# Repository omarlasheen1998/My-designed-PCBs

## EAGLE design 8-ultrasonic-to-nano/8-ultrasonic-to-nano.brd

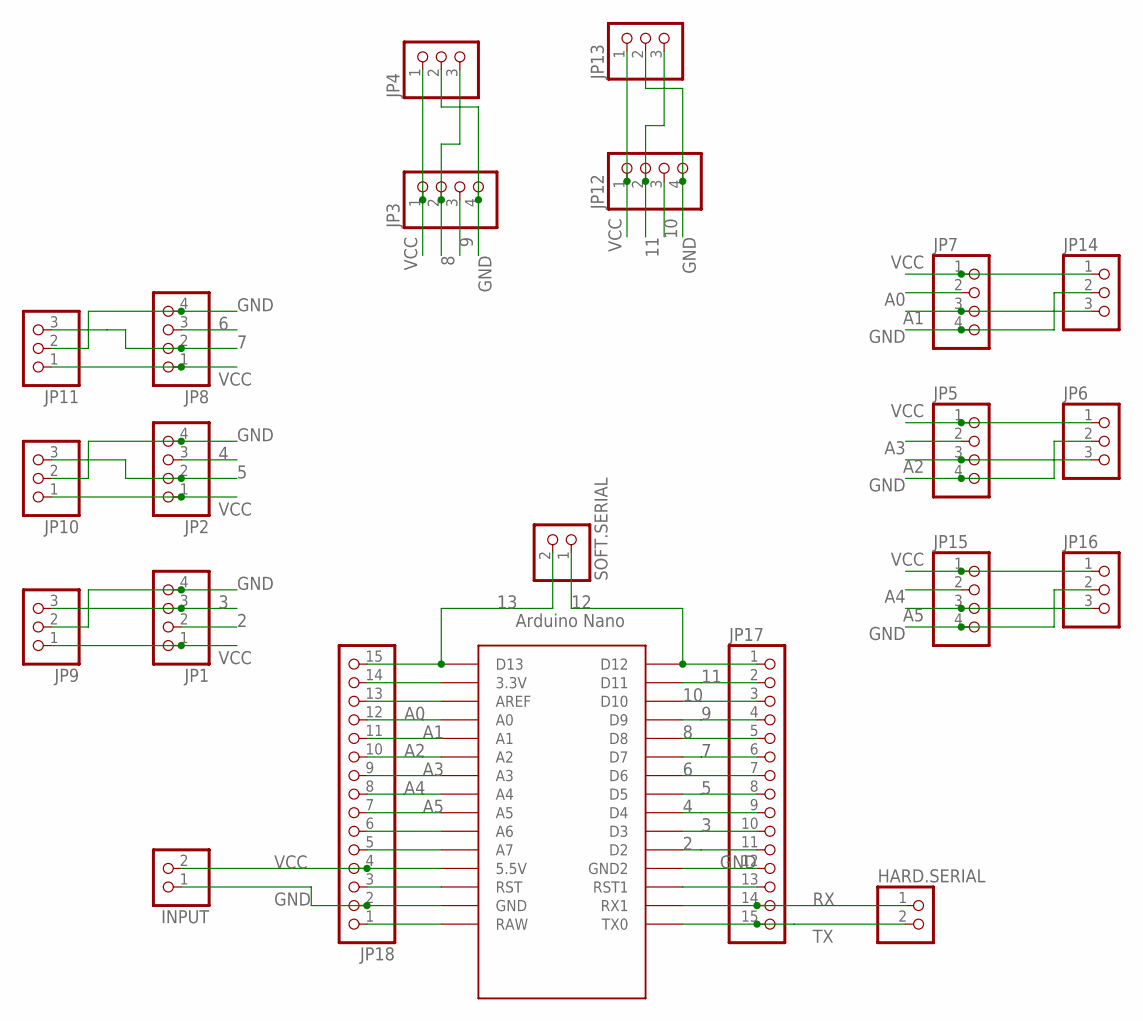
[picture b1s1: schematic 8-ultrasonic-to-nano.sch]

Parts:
HARD.SERIAL: PINHD-2_DATA; 1X02_DATA
INPUT: PINHD-2_DATA; 1X02_DATA
JP1, JP2, JP3, JP5, JP7, JP8, JP12, JP15: PINHD-4_DATA; 1X04_DATA
JP4, JP6, JP9, JP10, JP11, JP13, JP14, JP16: PINHD-3_DATA; 1X03_DATA
JP17, JP18: PINHD-1X15; 1X15
SOFT.SERIAL: PINHD-2_DATA; 1X02_DATA
U$1: ARDUINO_NANO; NANO

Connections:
2: JP1.2, JP17.11, U$1.D2
3: JP1.3, JP9.3, JP17.10, U$1.D3
4: JP2.3, JP17.9, U$1.D4
5: JP2.2, JP10.3, JP17.8, U$1.D5
6: JP8.3, JP17.7, U$1.D6
7: JP8.2, JP11.3, JP17.6, U$1.D7
8: JP3.2, JP4.3, JP17.5, U$1.D8
9: JP3.3, JP17.4, U$1.D9
10: JP12.3, JP17.3, U$1.D10
11: JP12.2, JP13.3, JP17.2, U$1.D11
12: JP17.1, SOFT.SERIAL.1, U$1.D12
13: JP18.15, SOFT.SERIAL.2, U$1.D13
A0: JP7.2, JP18.12, U$1.A0
A1: JP7.3, JP14.3, JP18.11, U$1.A1
A2: JP5.3, JP6.3, JP18.10, U$1.A2
A3: JP5.2, JP18.9, U$1.A3
A4: JP15.2, JP18.8, U$1.A4
A5: JP15.3, JP16.3, JP18.7, U$1.A5
GND: INPUT.1, JP1.4, JP2.4, JP3.4, JP4.2, JP5.4, JP6.2, JP7.4, JP8.4, JP9.2, JP10.2, JP11.2, JP12.4, JP13.2, JP14.2, JP15.4, JP16.2, JP17.12, JP18.2, U$1.GND, U$1.GND1 (GND2)
unnamed: JP17.13, U$1.RST1
unnamed: JP18.14, U$1.3.3V
unnamed: JP18.13, U$1.AREF
unnamed: JP18.6, U$1.A6
unnamed: JP18.5, U$1.A7
unnamed: JP18.3, U$1.RST
unnamed: JP18.1, U$1.RAW
RX: HARD.SERIAL.1, JP17.14, U$1.RX1
TX: HARD.SERIAL.2, JP17.15, U$1.TX0
VCC: INPUT.2, JP1.1, JP2.1, JP3.1, JP4.1, JP5.1, JP6.1, JP7.1, JP8.1, JP9.1, JP10.1, JP11.1, JP12.1, JP13.1, JP14.1, JP15.1, JP16.1, JP18.4, U$1.5V (5.5V)

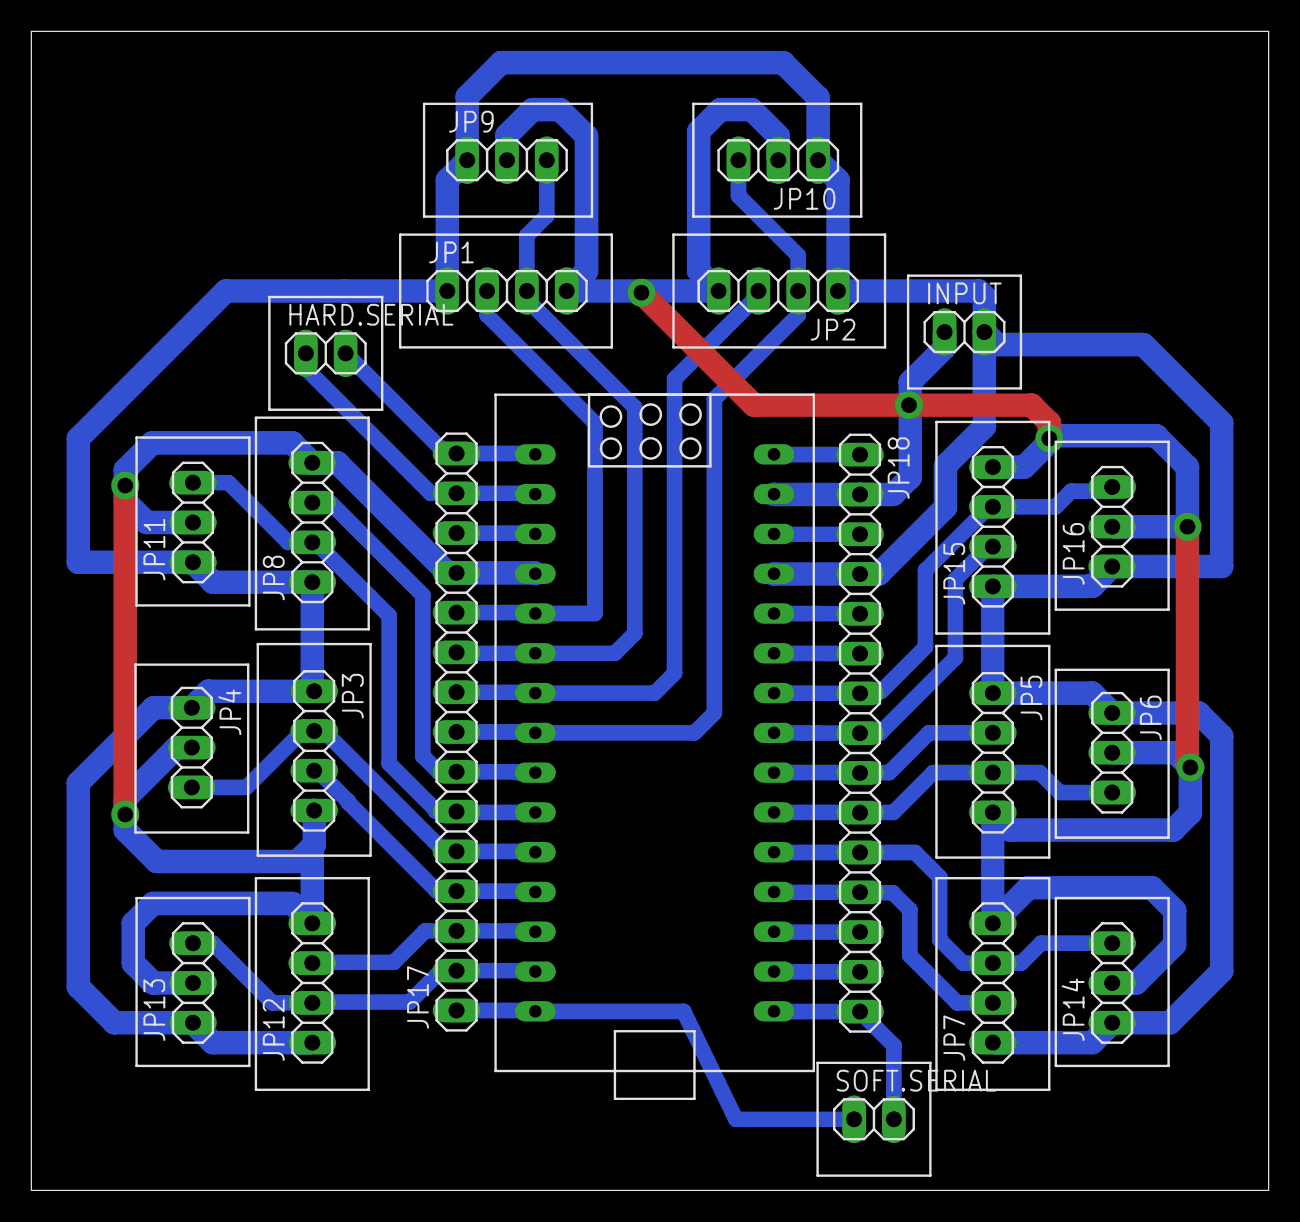
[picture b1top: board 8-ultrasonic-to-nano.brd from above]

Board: 2 copper layers, 79.0 x 74.0 mm, 22 parts (0 on the bottom side), 29 nets.

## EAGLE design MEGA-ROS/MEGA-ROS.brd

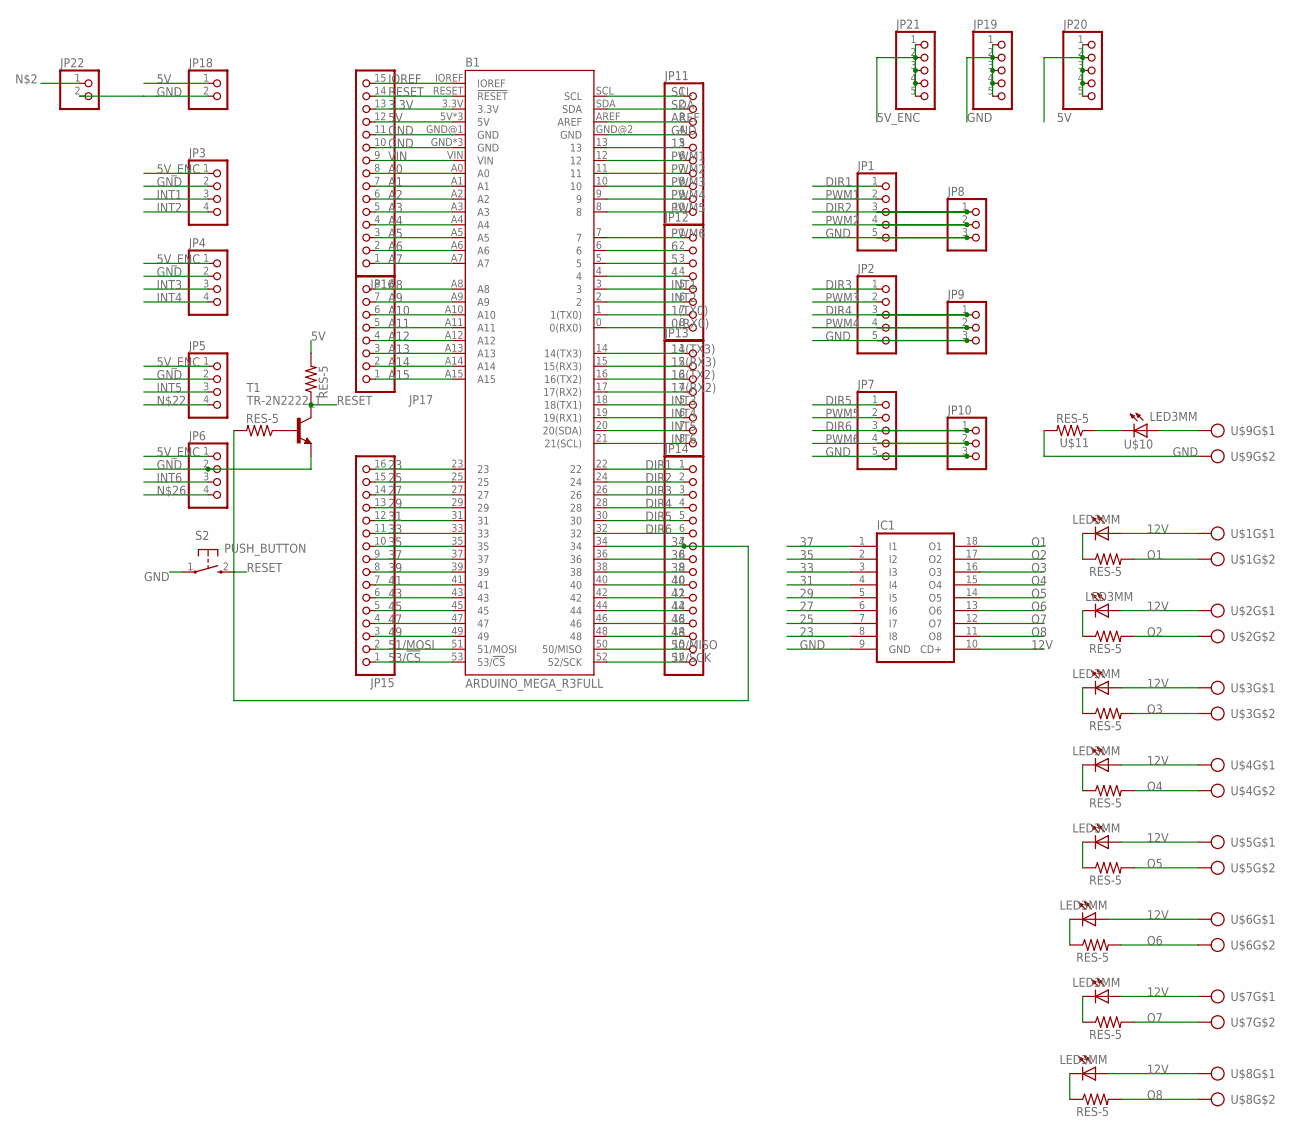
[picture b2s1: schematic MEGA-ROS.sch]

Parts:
B1: ARDUINO_MEGA_R3FULL; ARDUINO_MEGA_NO_SILK
IC1: ULN2803A; DIL18
JP1, JP2, JP7: PINHD-5_DATA; 1X05_DATA
JP3, JP4, JP5, JP6: PINHD-4_DATA; 1X04_DATA
JP8, JP9, JP10: PINHD-3_DATA; 1X03_DATA
JP11: PINHD-1X10; 1X10
JP12, JP13, JP17: PINHD-1X8; 1X08
JP14, JP15: PINHD-1X16; 1X16
JP16: PINHD-1X15; 1X15
JP18, JP22: PINHD-2_DATA; 1X02_DATA
JP19, JP20, JP21: PINHD-1X5; 1X05
S2: PUSH_BUTTON; B3F-10XX
T1: TR-2N2222_1; TO92-EBC
U$1, U$2, U$3, U$4, U$5, U$6, U$7, U$8, U$9: CON_PTR_2; AK300/2
U$10, U$12, U$14, U$16, U$18, U$20, U$22, U$24, U$26: LED3MM
U$11, U$13, U$15, U$17, U$19, U$21, U$23, U$25, U$27, U$28, U$29: RES-5; 0204/5

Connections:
0(RX0): B1.0 (0(RX0)), JP12.8
1(TX0): B1.1 (1(TX0)), JP12.7
3.3V: B1.3.3V, JP16.13
4: B1.4, JP12.4
5: B1.5, JP12.3
5V: B1.5V, B1.5V@1 (5V), B1.5V@2 (5V), JP16.12, JP18.1, JP20.1, JP20.2, JP20.3, JP20.4, JP20.5, U$28.2
5V_ENC: JP3.1, JP4.1, JP5.1, JP6.1, JP21.1, JP21.2, JP21.3, JP21.4, JP21.5
6: B1.6, JP12.2
12V: IC1.10 (CD+), U$1.1, U$2.1, U$3.1, U$4.1, U$5.1, U$6.1, U$7.1, U$8.1, U$12.A, U$14.A, U$16.A, U$18.A, U$20.A, U$22.A, U$24.A, U$26.A
13: B1.13, JP11.5
14(TX3): B1.14 (14(TX3)), JP13.1
15(RX3): B1.15 (15(RX3)), JP13.2
16(TX2): B1.16 (16(TX2)), JP13.3
17(RX2): B1.17 (17(RX2)), JP13.4
23: B1.23, IC1.8 (I8), JP15.16
25: B1.25, IC1.7 (I7), JP15.15
27: B1.27, IC1.6 (I6), JP15.14
29: B1.29, IC1.5 (I5), JP15.13
31: B1.31, IC1.4 (I4), JP15.12
33: B1.33, IC1.3 (I3), JP15.11
34: B1.34, JP14.7, U$29.2
35: B1.35, IC1.2 (I2), JP15.10
36: B1.36, JP14.8
37: B1.37, IC1.1 (I1), JP15.9
38: B1.38, JP14.9
39: B1.39, JP15.8
40: B1.40, JP14.10
41: B1.41, JP15.7
42: B1.42, JP14.11
43: B1.43, JP15.6
44: B1.44, JP14.12
45: B1.45, JP15.5
46: B1.46, JP14.13
47: B1.47, JP15.4
48: B1.48, JP14.14
49: B1.49, JP15.3
50/MISO: B1.50 (50/MISO), JP14.15
51/MOSI: B1.51 (51/MOSI), JP15.2
52/SCK: B1.52 (52/SCK), JP14.16
53/!CS: B1.53 (53/!CS), JP15.1
A0: B1.A0, JP16.8
A1: B1.A1, JP16.7
A2: B1.A2, JP16.6
A3: B1.A3, JP16.5
A4: B1.A4, JP16.4
A5: B1.A5, JP16.3
A6: B1.A6, JP16.2
A7: B1.A7, JP16.1
A8: B1.A8, JP17.8
A9: B1.A9, JP17.7
A10: B1.A10, JP17.6
A11: B1.A11, JP17.5
A12: B1.A12, JP17.4
A13: B1.A13, JP17.3
A14: B1.A14, JP17.2
A15: B1.A15, JP17.1
AREF: B1.AREF, JP11.3
DIR1: B1.22, JP1.1, JP14.1
DIR2: B1.24, JP1.3, JP8.1, JP14.2
DIR3: B1.26, JP2.1, JP14.3
DIR4: B1.28, JP2.3, JP9.1, JP14.4
DIR5: B1.30, JP7.1, JP14.5
DIR6: B1.32, JP7.3, JP10.1, JP14.6
GND: B1.GND, B1.GND@1 (GND), B1.GND@2 (GND), B1.GND@3 (GND), B1.GND@4 (GND), IC1.9 (GND), JP1.5, JP2.5, JP3.2, JP4.2, JP5.2, JP6.2, JP7.5, JP8.3, JP9.3, JP10.3, JP11.4, JP16.10, JP16.11, JP18.2, JP19.1, JP19.2, JP19.3, JP19.4, JP19.5, JP22.2, S2.1, T1.E, U$9.2, U$11.2
INT1: B1.3, JP3.3, JP12.5
INT2: B1.2, JP3.4, JP12.6
INT3: B1.18 (18(TX1)), JP4.3, JP13.5
INT4: B1.19 (19(RX1)), JP4.4, JP13.6
INT5: B1.20 (20(SDA)), JP5.3, JP13.7
INT6: B1.21 (21(SCL)), JP6.3, JP13.8
IOREF: B1.IOREF, JP16.15
unnamed: U$10.K (C), U$11.1
unnamed: U$12.K (C), U$13.1
unnamed: U$14.K (C), U$15.1
unnamed: U$16.K (C), U$17.1
unnamed: U$18.K (C), U$19.1
unnamed: U$20.K (C), U$21.1
unnamed: U$22.K (C), U$23.1
unnamed: U$24.K (C), U$25.1
unnamed: U$26.K (C), U$27.1
unnamed: U$9.1, U$10.A
unnamed: T1.B, U$29.1
O1: IC1.18 (O1), U$1.2, U$13.2
O2: IC1.17 (O2), U$2.2, U$15.2
O3: IC1.16 (O3), U$3.2, U$17.2
O4: IC1.15 (O4), U$4.2, U$19.2
O5: IC1.14 (O5), U$5.2, U$21.2
O6: IC1.13 (O6), U$6.2, U$23.2
O7: IC1.12 (O7), U$7.2, U$25.2
O8: IC1.11 (O8), U$8.2, U$27.2
PWM1: B1.12, JP1.2, JP11.6
PWM2: B1.11, JP1.4, JP8.2, JP11.7
PWM3: B1.10, JP2.2, JP11.8
PWM4: B1.9, JP2.4, JP9.2, JP11.9
PWM5: B1.8, JP7.2, JP11.10
PWM6: B1.7, JP7.4, JP10.2, JP12.1
RESET: B1.RESET (!RESET), JP16.14, S2.2 (S), T1.C, U$28.1
SCL: B1.SCL, JP11.1
SDA: B1.SDA, JP11.2
VIN: B1.VIN, JP16.9

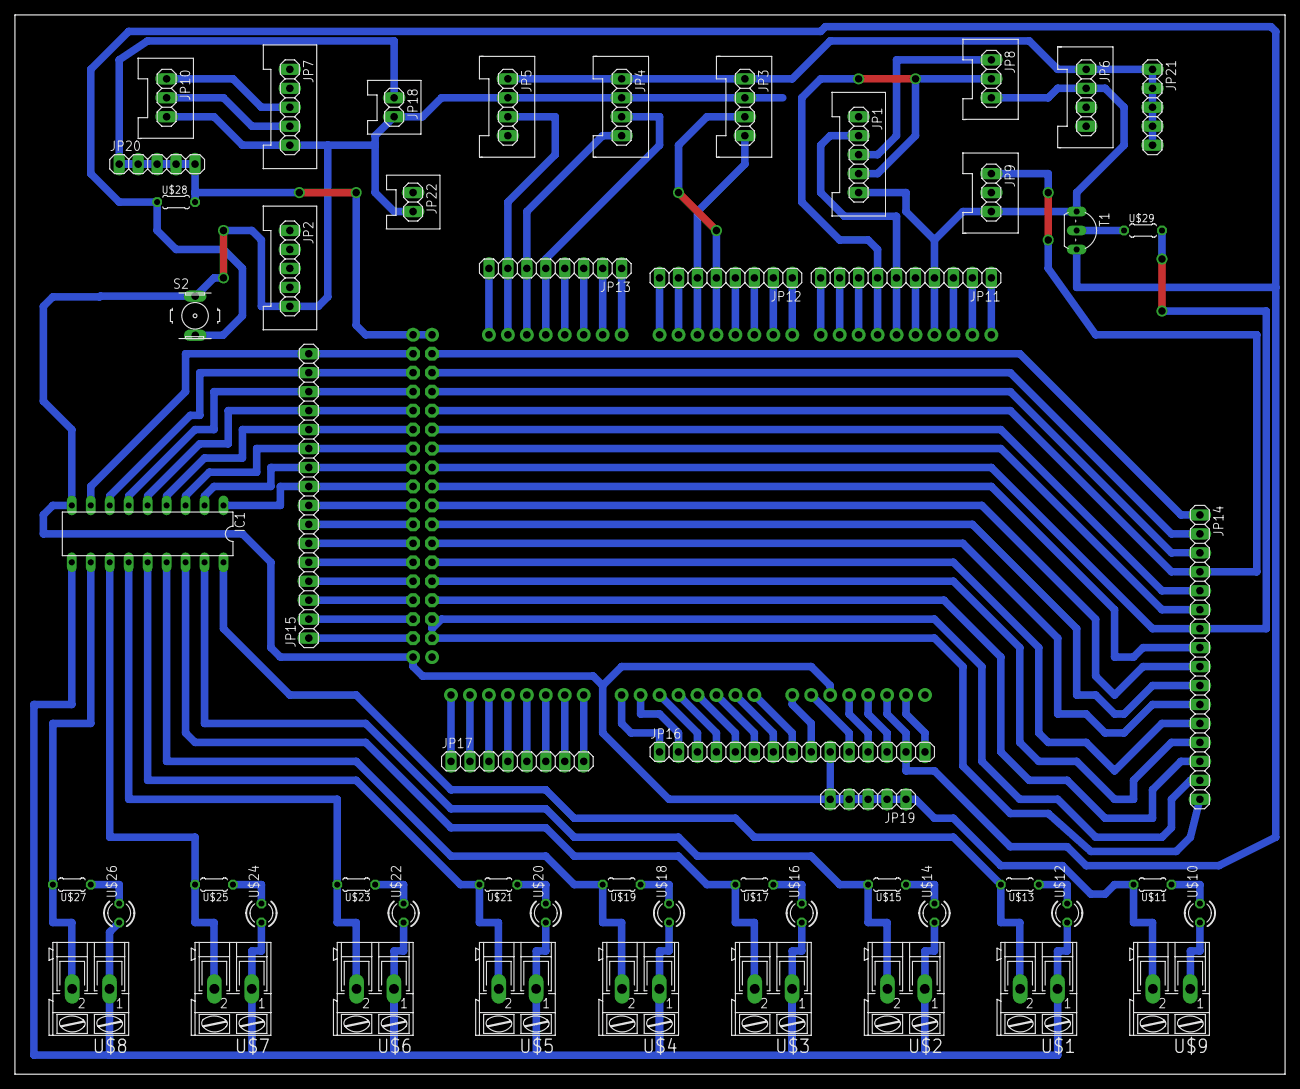
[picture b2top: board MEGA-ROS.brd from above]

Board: 2 copper layers, 170.2 x 141.9 mm, 55 parts (1 on the bottom side), 100 nets.

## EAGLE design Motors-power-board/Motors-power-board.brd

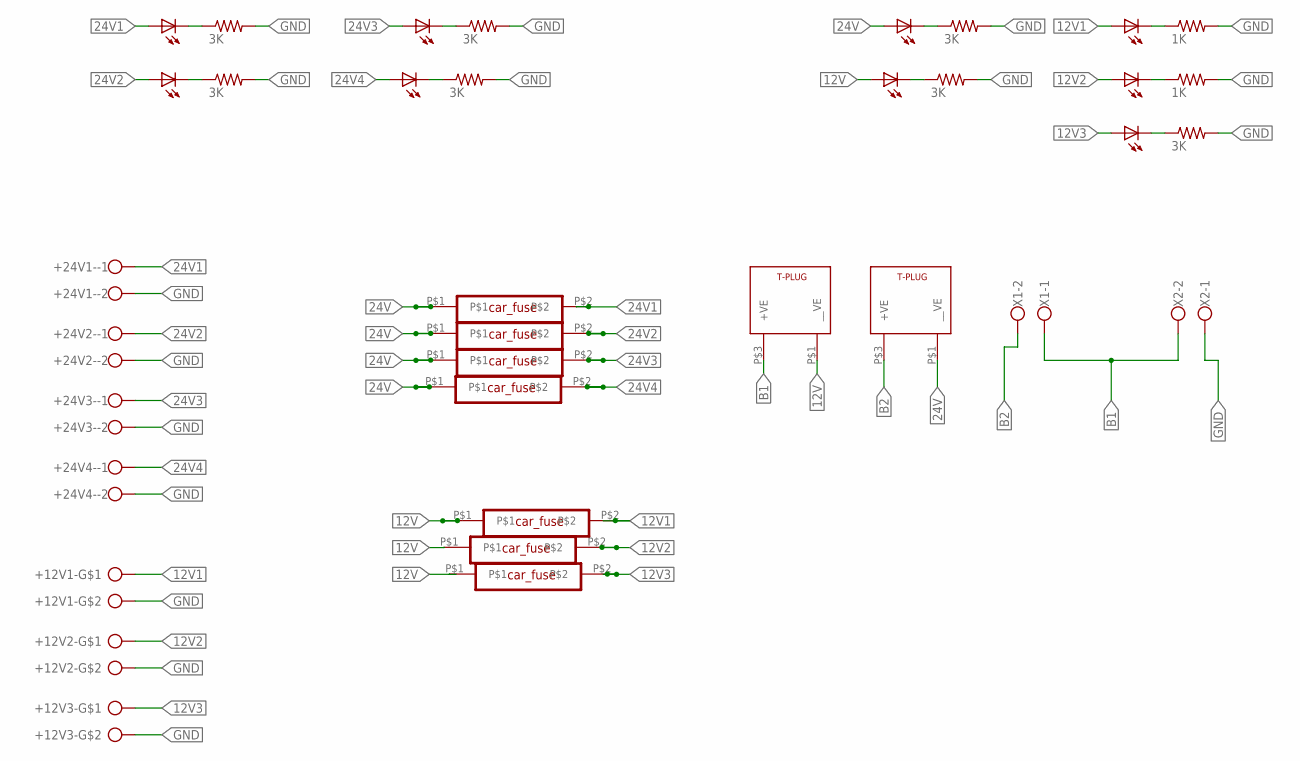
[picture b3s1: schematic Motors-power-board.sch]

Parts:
1K1: 3K; 0204/7
1K2: 1K; 0204/7
+12V1-, +12V2-, +12V3-: CON_PTR_2; AK300/2
+24V1-, +24V2-, +24V3-, +24V4-: ROSTA.POWER; W239-302
U$4, U$20, U$27, U$28: LED24V; LED3MM
U$5, U$6: T_CONNECTOR; T-PLUG
U$8, U$9, U$22, U$23, U$24, U$31: 3K; 0204/7
U$10, U$11, U$12, U$13, U$14, U$15, U$16: CAR_FUSE
U$18, U$25: LED5V2; LED3MM
U$19, U$26: LED5V1; LED3MM
U$21: LED12V; LED3MM
U$29: 1K; 0204/7
X1, X2: ROSTA.POWER; W239-302

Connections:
12V: U$5.P$1 (__VE), U$14.P$1, U$15.P$1, U$16.P$1, U$28.A
12V1: +12V1-.1, U$14.P$2, U$25.A
12V2: +12V2-.1, U$15.P$2, U$26.A
12V3: +12V3-.1, U$16.P$2, U$27.A
24V: U$4.A, U$6.P$1 (__VE), U$10.P$1, U$11.P$1, U$12.P$1, U$13.P$1
24V1: +24V1-.1, U$10.P$2, U$18.A
24V2: +24V2-.1, U$11.P$2, U$19.A
24V3: +24V3-.1, U$12.P$2, U$20.A
24V4: +24V4-.1, U$13.P$2, U$21.A
B1: U$5.P$3 (+VE), X1.1, X2.2
B2: U$6.P$3 (+VE), X1.2
GND: 1K1.2, 1K2.2, +12V1-.2, +12V2-.2, +12V3-.2, +24V1-.2, +24V2-.2, +24V3-.2, +24V4-.2, U$8.2, U$9.2, U$22.2, U$23.2, U$24.2, U$29.2, U$31.2, X2.1
unnamed: 1K1.1, U$18.K (C)
unnamed: U$19.K (C), U$22.1
unnamed: U$21.K (C), U$23.1
unnamed: U$20.K (C), U$24.1
unnamed: 1K2.1, U$25.K (C)
unnamed: U$26.K (C), U$29.1
unnamed: U$8.1, U$28.K (C)
unnamed: U$4.K (C), U$9.1
unnamed: U$27.K (C), U$31.1

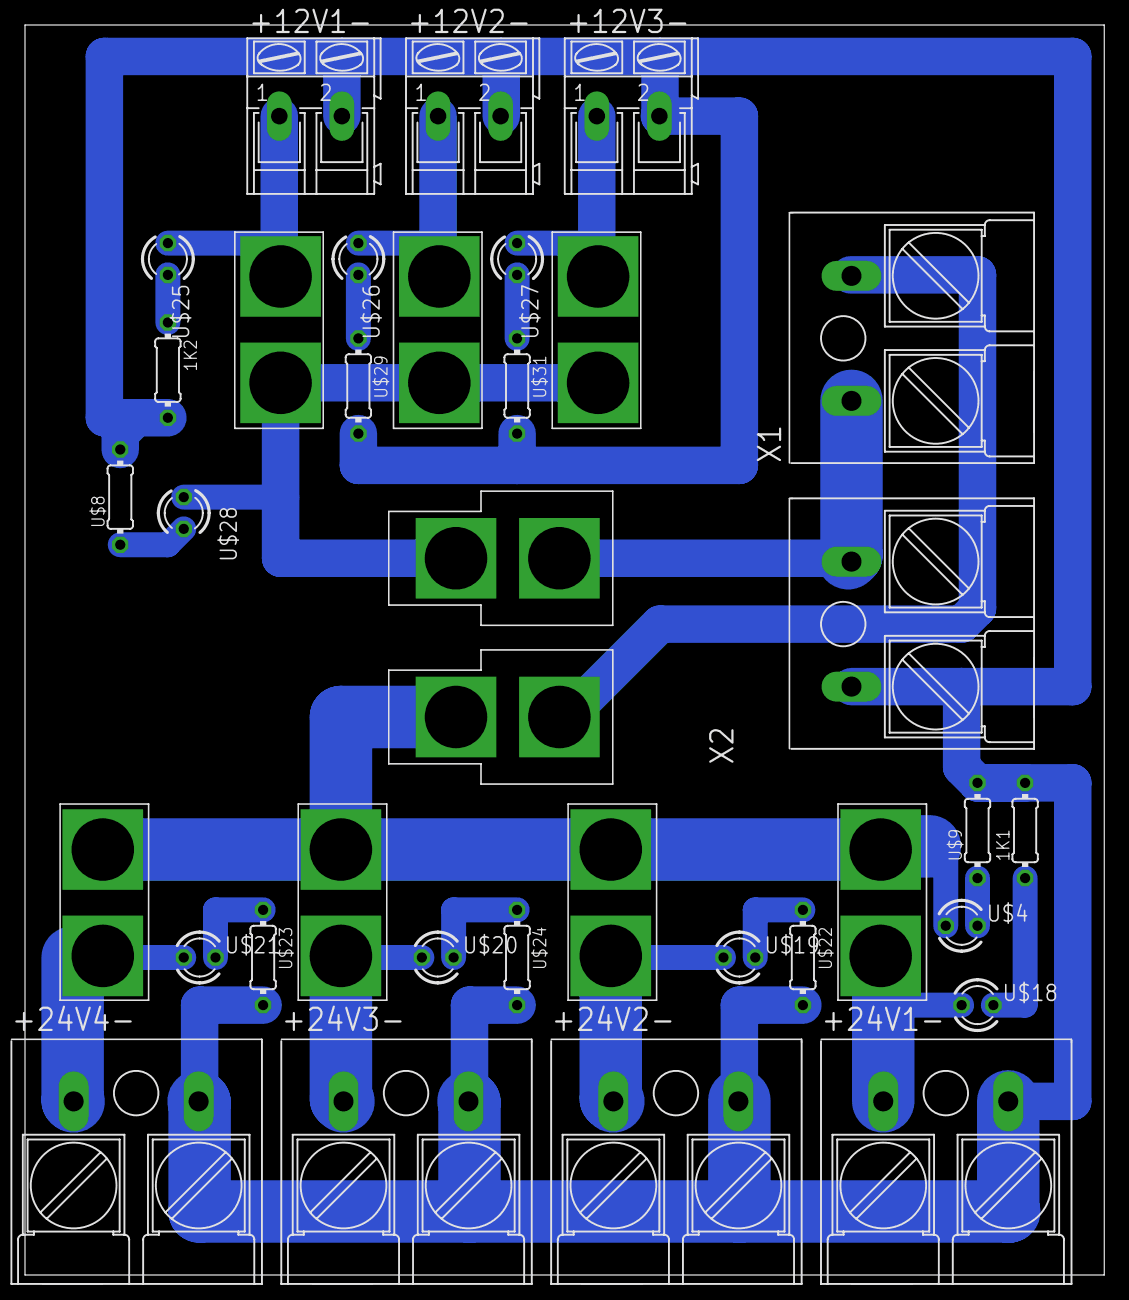
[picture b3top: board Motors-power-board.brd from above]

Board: 2 copper layers, 86.3 x 100.0 mm, 36 parts (0 on the bottom side), 21 nets.

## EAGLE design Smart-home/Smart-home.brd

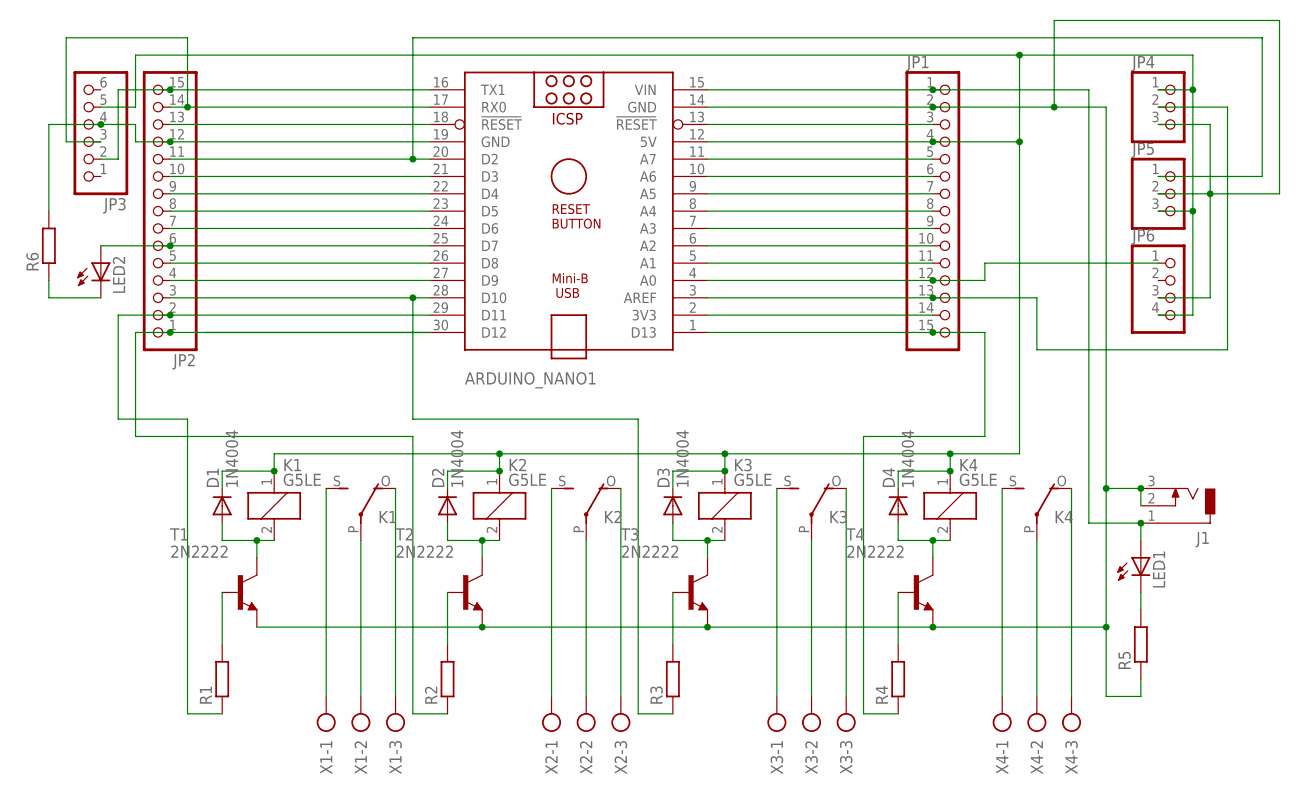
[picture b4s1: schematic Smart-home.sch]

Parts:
ARDUINO_NANO1: ARDUINO_NANO
D1, D2, D3, D4: 1N4004; DO41-10
J1: DCJ0303
JP1, JP2: PINHD-1X15; 1X15
JP3: PINHD-1X6; 1X06
JP4, JP5: PINHD-1X3; 1X03
JP6: PINHD-1X4; 1X04
K1, K2, K3, K4: G5LE
LED1, LED2: LED3MM
R1, R2, R3, R4, R5, R6: R-EU_0204/7; 0204/7
T1, T2, T3, T4: 2N2222; TO18
X1, X2, X3, X4: AK300/3

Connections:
unnamed: D1.A, K1.2, T1.3 (C)
unnamed: ARDUINO_NANO1.17 (RX0), JP2.14, JP3.3
unnamed: D2.A, K2.2, T2.3 (C)
unnamed: D3.A, K3.2, T3.3 (C)
unnamed: D4.A, K4.2, T4.3 (C)
unnamed: ARDUINO_NANO1.30 (D12), JP2.1, R2.1
unnamed: R1.2, T1.2 (B)
unnamed: ARDUINO_NANO1.1 (D13), JP1.15, R4.1
unnamed: ARDUINO_NANO1.28 (D10), JP2.3, R3.1
unnamed: ARDUINO_NANO1.16 (TX1), JP2.15, JP3.2
unnamed: ARDUINO_NANO1.14 (GND), J1.2, J1.3, JP1.2, JP4.3, JP5.2, JP6.3, R5.1, T1.1 (E), T2.1 (E), T3.1 (E), T4.1 (E)
unnamed: ARDUINO_NANO1.18 (!RESET), JP2.13
unnamed: ARDUINO_NANO1.19 (GND), JP2.12, JP3.4, R6.2
unnamed: ARDUINO_NANO1.20 (D2), JP2.11, JP5.1
unnamed: ARDUINO_NANO1.21 (D3), JP2.10
unnamed: ARDUINO_NANO1.22 (D4), JP2.9
unnamed: ARDUINO_NANO1.23 (D5), JP2.8
unnamed: ARDUINO_NANO1.24 (D6), JP2.7
unnamed: ARDUINO_NANO1.25 (D7), JP2.6, LED2.A
unnamed: ARDUINO_NANO1.26 (D8), JP2.5
unnamed: ARDUINO_NANO1.27 (D9), JP2.4
unnamed: ARDUINO_NANO1.3 (AREF), JP1.13, JP4.2
unnamed: ARDUINO_NANO1.11 (A7), JP1.5
unnamed: ARDUINO_NANO1.5 (A1), JP1.11
unnamed: ARDUINO_NANO1.6 (A2), JP1.10
unnamed: ARDUINO_NANO1.7 (A3), JP1.9
unnamed: ARDUINO_NANO1.8 (A4), JP1.8
unnamed: ARDUINO_NANO1.9 (A5), JP1.7
unnamed: ARDUINO_NANO1.10 (A6), JP1.6
unnamed: LED2.K (C), R6.1
unnamed: K1.O, X1.3
unnamed: ARDUINO_NANO1.13 (!RESET), JP1.3
unnamed: ARDUINO_NANO1.2 (3V3), JP1.14
unnamed: ARDUINO_NANO1.4 (A0), JP1.12, JP6.1
unnamed: K1.P, X1.2
unnamed: ARDUINO_NANO1.12 (5V), D1.C, D2.C, D3.C, D4.C, JP1.4, JP3.5, JP4.1, JP5.3, JP6.4, K1.1, K2.1, K3.1, K4.1
unnamed: K1.S, X1.1
unnamed: K2.S, X2.1
unnamed: K2.P, X2.2
unnamed: K2.O, X2.3
unnamed: K3.P, X3.2
unnamed: K3.O, X3.3
unnamed: K3.S, X3.1
unnamed: K4.S, X4.1
unnamed: K4.P, X4.2
unnamed: K4.O, X4.3
unnamed: ARDUINO_NANO1.29 (D11), JP2.2, R1.1
unnamed: R2.2, T2.2 (B)
unnamed: R3.2, T3.2 (B)
unnamed: R4.2, T4.2 (B)
unnamed: ARDUINO_NANO1.15 (VIN), J1.1, JP1.1, LED1.A
unnamed: LED1.K (C), R5.2

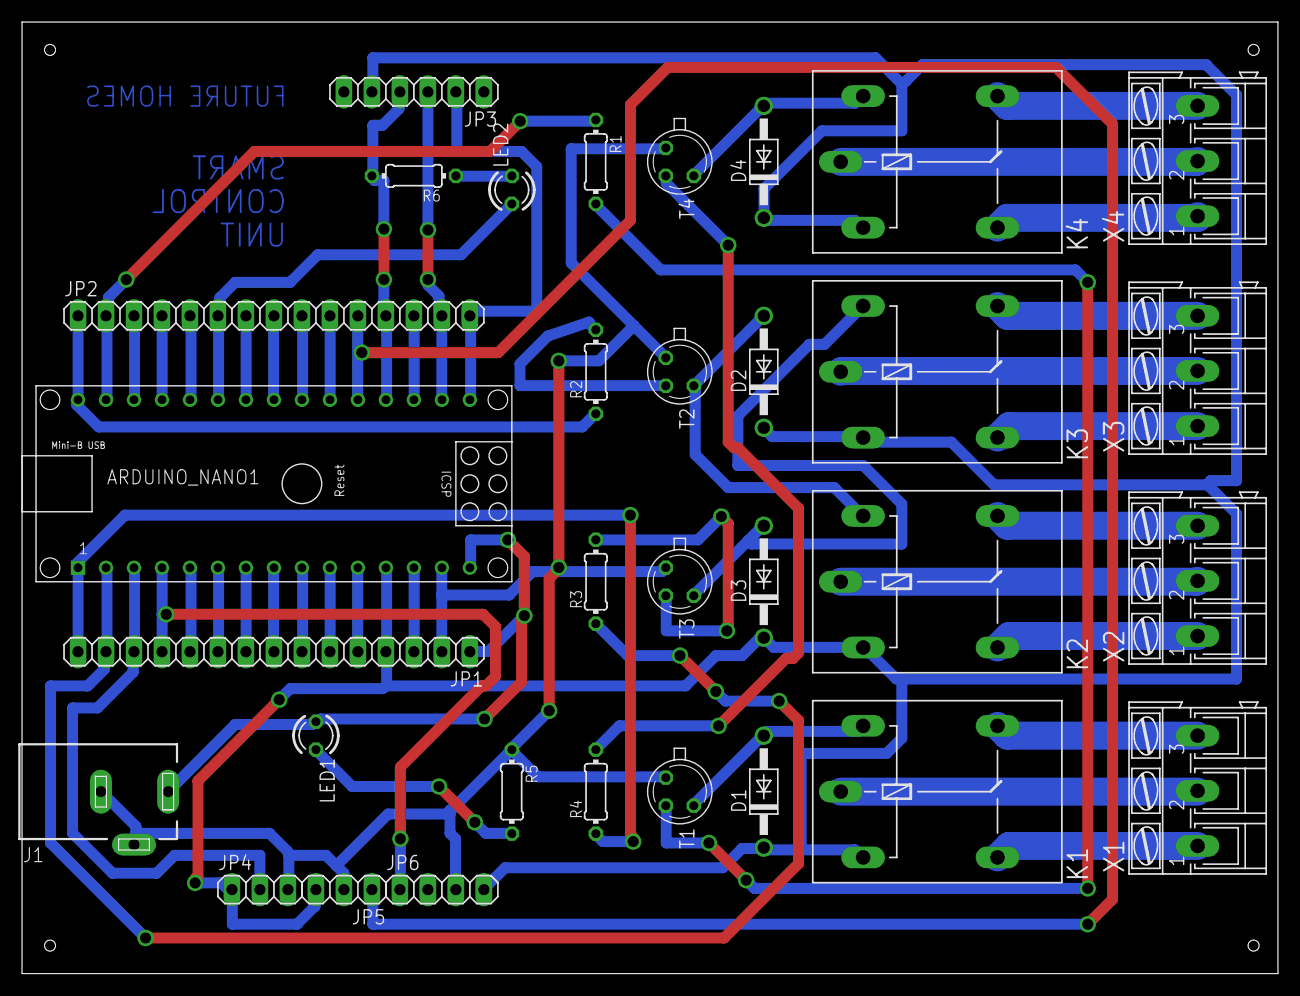
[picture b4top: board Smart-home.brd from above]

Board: 2 copper layers, 114.0 x 86.4 mm, 32 parts (0 on the bottom side), 52 nets.

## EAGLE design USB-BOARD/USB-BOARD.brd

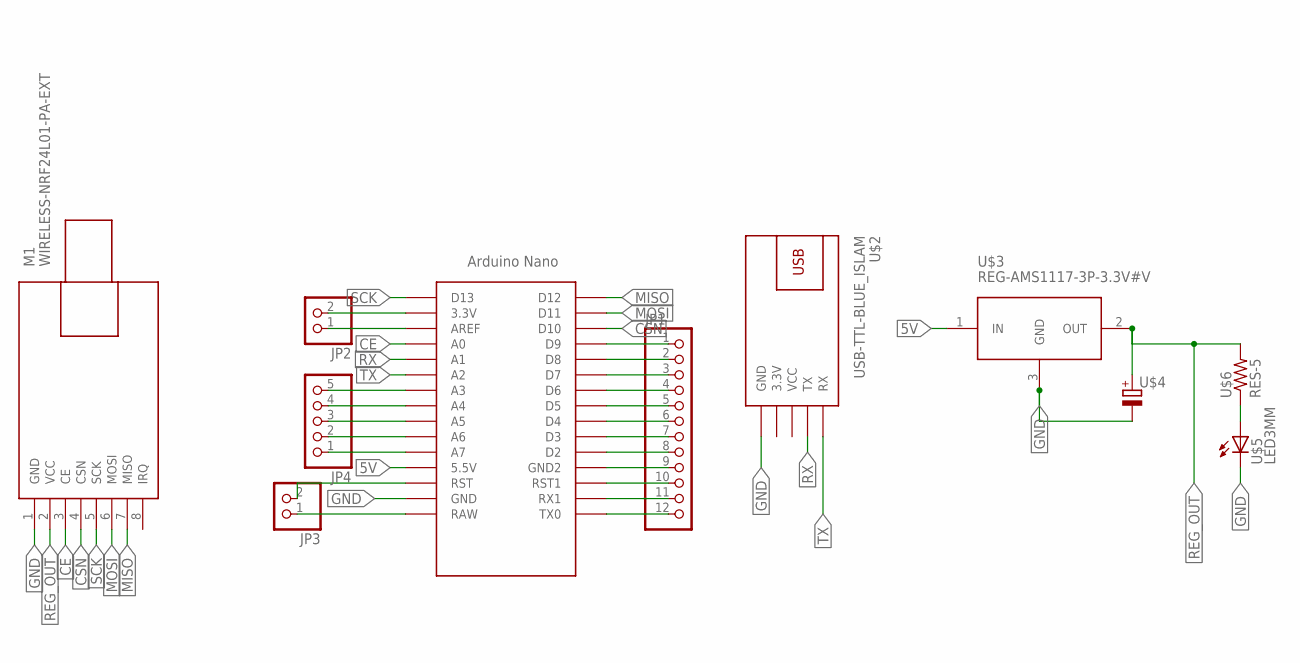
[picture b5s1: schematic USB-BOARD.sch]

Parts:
JP1: PINHD-1X12; 1X12
JP2, JP3: PINHD-1X2; 1X02
JP4: PINHD-1X5; 1X05
M1: WIRELESS-NRF24L01-PA-EXT
U$1: ARDUINO_NANO; NANO
U$2: USB-TTL-BLUE_ISLAM; USB-TTL-BLUE
U$3: REG-AMS1117-3P-3.3V#V; REG-AMS1117-3P#V
U$4: CAP_POL; E3,5-8
U$5: LED3MM
U$6: RES-5; 0204/5

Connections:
5V: U$1.5V (5.5V), U$3.1 (IN)
CE: M1.3 (CE), U$1.A0
CSN: M1.4 (CSN), U$1.D10
GND: M1.1 (GND), U$1.GND, U$2.GND, U$3.3 (GND), U$4.-, U$5.K (C)
MISO: M1.7 (MISO), U$1.D12
MOSI: M1.6 (MOSI), U$1.D11
unnamed: JP2.2, U$1.3.3V
unnamed: JP2.1, U$1.AREF
unnamed: JP4.5, U$1.A3
unnamed: JP4.4, U$1.A4
unnamed: JP4.3, U$1.A5
unnamed: JP4.2, U$1.A6
unnamed: JP4.1, U$1.A7
unnamed: JP3.2, U$1.RST
unnamed: JP3.1, U$1.RAW
unnamed: JP1.12, U$1.TX0
unnamed: JP1.11, U$1.RX1
unnamed: JP1.10, U$1.RST1
unnamed: JP1.9, U$1.GND1 (GND2)
unnamed: JP1.8, U$1.D2
unnamed: JP1.7, U$1.D3
unnamed: JP1.6, U$1.D4
unnamed: JP1.5, U$1.D5
unnamed: JP1.4, U$1.D6
unnamed: JP1.3, U$1.D7
unnamed: JP1.2, U$1.D8
unnamed: JP1.1, U$1.D9
unnamed: U$5.A, U$6.1
REG_OUT: M1.2 (VCC), U$3.2 (OUT), U$4.+, U$6.2
RX: U$1.A1, U$2.TX
SCK: M1.5 (SCK), U$1.D13
TX: U$1.A2, U$2.RX
VCC: U$2.VCC

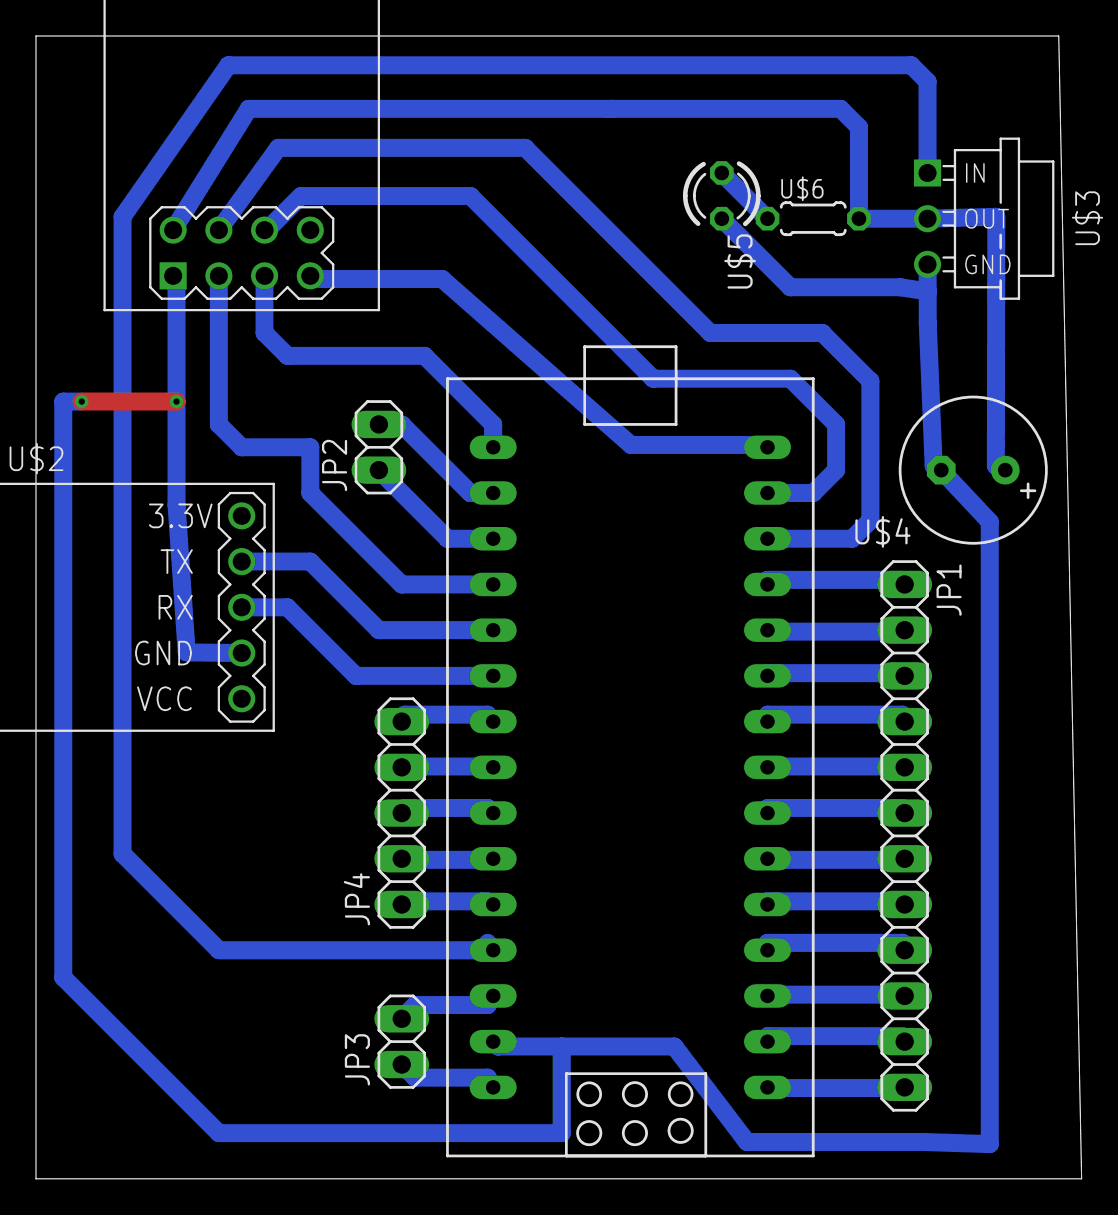
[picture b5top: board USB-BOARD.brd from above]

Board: 2 copper layers, 58.1 x 63.5 mm, 11 parts (0 on the bottom side), 32 nets.

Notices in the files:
parts and their libraries:
SparkFun-Boards: Licensing: Creative Commons ShareAlike 4.0 International - https://creativecommons.org/licenses/by-sa/4.0
diy-modules: Released under the Creative Commons Attribution 4.0 International License: http://creativecommons.org/licenses/by/4.0
